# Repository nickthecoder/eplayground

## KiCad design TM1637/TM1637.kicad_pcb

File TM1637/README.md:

TM1637
======

The TM1637 can drive six eight segment displays, or a 6x8 LED matrix, as well as upto 16 buttons.

The module only has 8 buttons, however, you can switch between the two banks of buttons using a switch.

The outputs for the leds are exposed as simple header pins.

## Version History

### Version 1.0

At the time of writing, I haven't tested this module.

The name of the module is missing. It reads "Module Name". Oops.

### Version 1.1

Not printed.

Renamed the directory.
Corrected the module name.

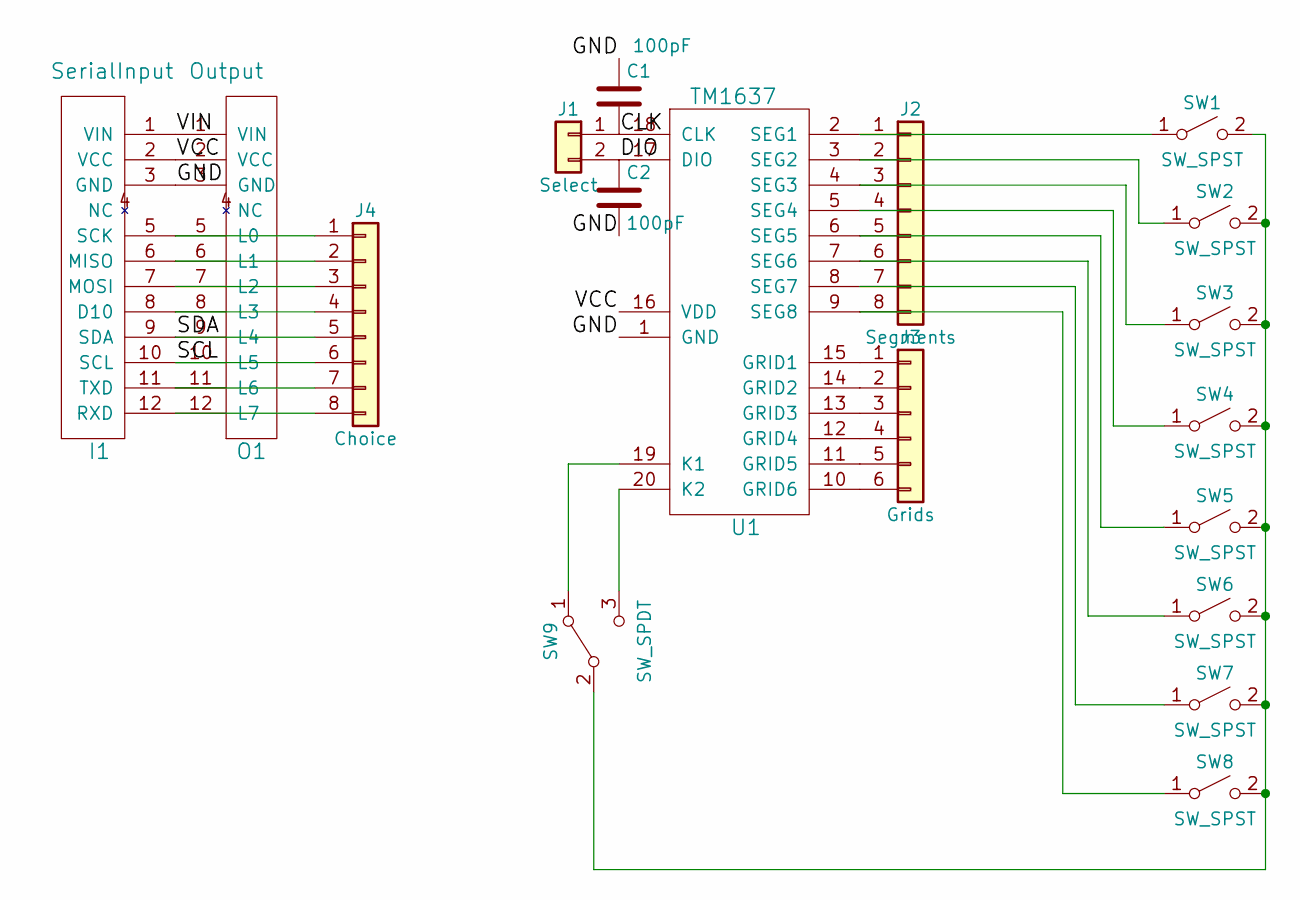
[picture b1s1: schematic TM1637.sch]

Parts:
C1, C2: 100pF; C_Disc_D3.0mm_W1.6mm_P2.50mm
I1: SerialInput; Pin_Header_Straight_1x12_Pitch2.54mm
J1: Select; Pin_Header_Straight_1x02_Pitch2.54mm
J2: Segments; Pin_Header_Straight_1x08_Pitch2.54mm
J3: Grids; Pin_Header_Straight_1x06_Pitch2.54mm
J4: Choice; Pin_Header_Straight_1x08_Pitch2.54mm
O1: Output; Socket_Strip_Straight_1x12_Pitch2.54mm
SW1, SW2, SW3, SW4, SW5, SW6, SW7, SW8: SW_SPST; SW_SPST_EVQP0
SW9: SW_SPDT; SW_CuK_JS202011CQN_DPDT_Straight
U1: TM1637; DIP-20_W7.62mm

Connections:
/CLK: C1.2, J1.1, U1.18 (CLK)
/DIO: C2.1, J1.2, U1.17 (DIO)
/GND: C1.1, C2.2, I1.3 (GND), O1.3 (GND), U1.1 (GND)
/SCL: I1.10 (SCL), J4.6, O1.10 (L5)
/SDA: I1.9 (SDA), J4.5, O1.9 (L4)
/VCC: I1.2 (VCC), O1.2 (VCC), U1.16 (VDD)
/VIN: I1.1 (VIN), O1.1 (VIN)
unnamed: I1.5 (SCK), J4.1, O1.5 (L0)
unnamed: I1.6 (MISO), J4.2, O1.6 (L1)
unnamed: I1.7 (MOSI), J4.3, O1.7 (L2)
unnamed: I1.8 (D10), J4.4, O1.8 (L3)
unnamed: I1.11 (TXD), J4.7, O1.11 (L6)
unnamed: I1.12 (RXD), J4.8, O1.12 (L7)
unnamed: J2.1, SW1.1 (A), U1.2 (SEG1)
unnamed: J2.2, SW2.1 (A), U1.3 (SEG2)
unnamed: J2.3, SW3.1 (A), U1.4 (SEG3)
unnamed: J2.4, SW4.1 (A), U1.5 (SEG4)
unnamed: J2.5, SW5.1 (A), U1.6 (SEG5)
unnamed: J2.6, SW6.1 (A), U1.7 (SEG6)
unnamed: J2.7, SW7.1 (A), U1.8 (SEG7)
unnamed: J2.8, SW8.1 (A), U1.9 (SEG8)
unnamed: J3.1, U1.15 (GRID1)
unnamed: J3.2, U1.14 (GRID2)
unnamed: J3.3, U1.13 (GRID3)
unnamed: J3.4, U1.12 (GRID4)
unnamed: J3.5, U1.11 (GRID5)
unnamed: J3.6, U1.10 (GRID6)
unnamed: SW1.2 (B), SW2.2 (B), SW3.2 (B), SW4.2 (B), SW5.2 (B), SW6.2 (B), SW7.2 (B), SW8.2 (B), SW9.2 (B)
unnamed: SW9.1 (A), U1.19 (K1)
unnamed: SW9.3 (C), U1.20 (K2)

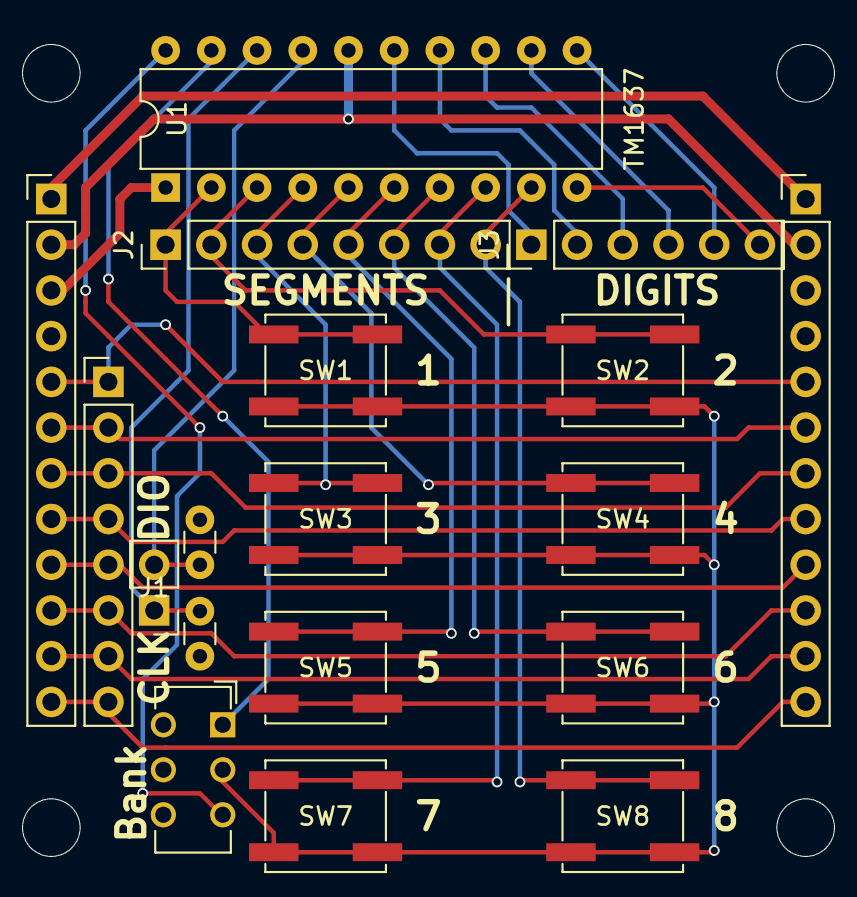
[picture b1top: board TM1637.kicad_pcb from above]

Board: 2 copper layers, 20 parts (0 on the bottom side), 30 nets.

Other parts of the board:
M3, M3#2: MountingHole_3.2mm_M3

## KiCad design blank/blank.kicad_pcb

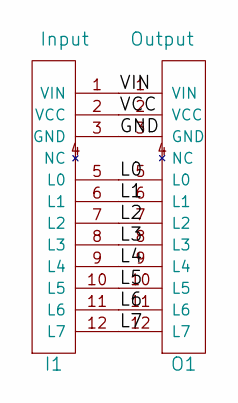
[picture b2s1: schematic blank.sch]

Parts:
I1: Input; Pin_Header_Straight_1x12_Pitch2.54mm
O1: Output; Socket_Strip_Straight_1x12_Pitch2.54mm

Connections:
/GND: I1.3 (GND), O1.3 (GND)
/L0: I1.5 (L0), O1.5 (L0)
/L1: I1.6 (L1), O1.6 (L1)
/L2: I1.7 (L2), O1.7 (L2)
/L3: I1.8 (L3), O1.8 (L3)
/L4: I1.9 (L4), O1.9 (L4)
/L5: I1.10 (L5), O1.10 (L5)
/L6: I1.11 (L6), O1.11 (L6)
/L7: I1.12 (L7), O1.12 (L7)
/VCC: I1.2 (VCC), O1.2 (VCC)
/VIN: I1.1 (VIN), O1.1 (VIN)

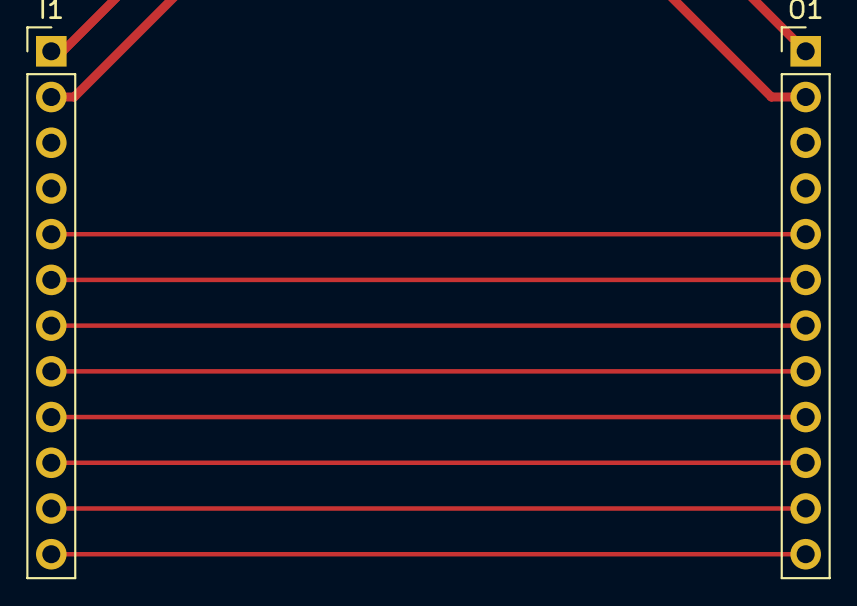
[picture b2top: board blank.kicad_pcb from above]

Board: 2 copper layers, 4 parts (0 on the bottom side), 11 nets.

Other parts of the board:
M3, M3#2: MountingHole_3.2mm_M3

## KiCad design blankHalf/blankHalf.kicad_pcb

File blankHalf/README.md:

I used this as a template for half-sized boards.
To keep costs low, I combine two half sized boards into one design, and have both printed
as if it were one board.

I have a router, which I can do my own V cuts, but its also easy to cut the boards using a sharp knife,
a little patience and brute force to snap them in two.

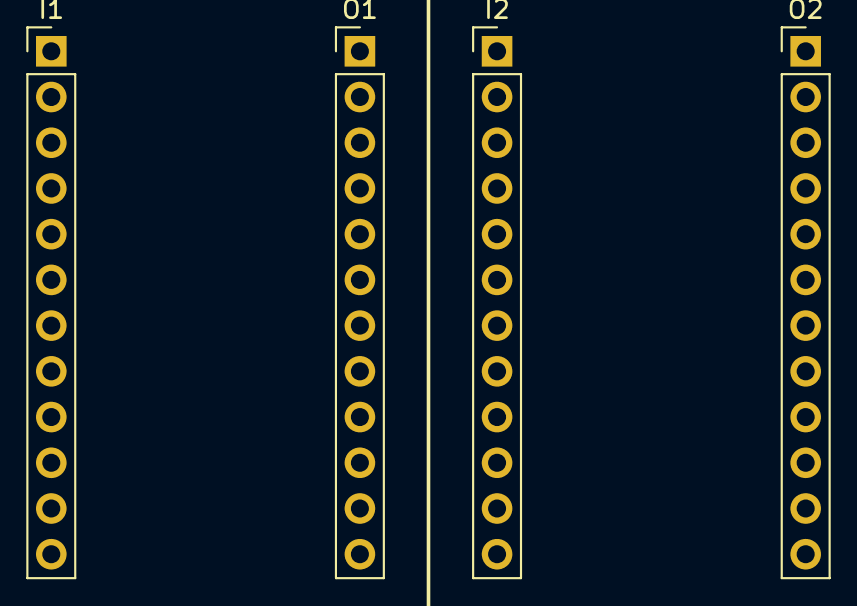
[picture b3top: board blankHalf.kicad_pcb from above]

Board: 2 copper layers, 6 parts (0 on the bottom side), 22 nets, no tracks yet.

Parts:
I1, I2: Input; Pin_Header_Straight_1x12_Pitch2.54mm
M3, M3#2: MountingHole_3.2mm_M3
O1, O2: Output; Socket_Strip_Straight_1x12_Pitch2.54mm

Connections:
/D0: I2.5, O2.5
/D1: I2.6, O2.6
/D2: I2.7, O2.7
/D3: I2.8, O2.8
/D4: I2.9, O2.9
/D5: I2.10, O2.10
/D6: I2.11, O2.11
/D7: I2.12, O2.12
/GND: I1.3, O1.3
/GND2: I2.3, O2.3
/L0: I1.5, O1.5
/L1: I1.6, O1.6
/L2: I1.7, O1.7
/L3: I1.8, O1.8
/L4: I1.9, O1.9
/L5: I1.10, O1.10
/L6: I1.11, O1.11
/L7: I1.12, O1.12
/VCC: I1.2, O1.2
/VCC2: I2.2, O2.2
/VIN: I1.1, O1.1
/VIN2: I2.1, O2.1

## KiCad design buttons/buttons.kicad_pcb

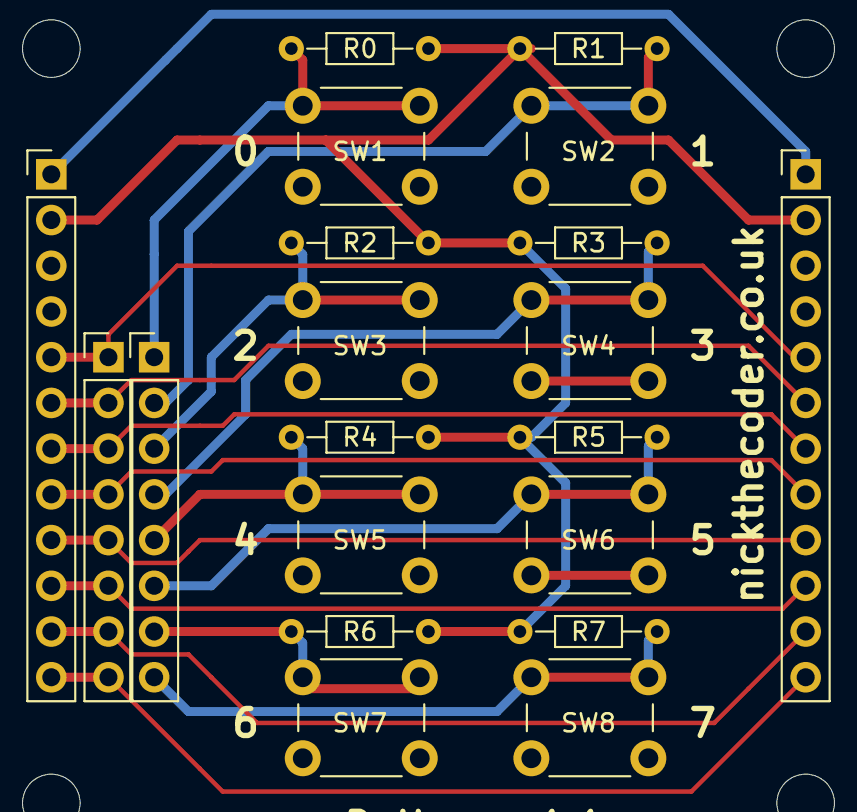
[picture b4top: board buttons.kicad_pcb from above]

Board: 2 copper layers, 22 parts (0 on the bottom side), 19 nets.

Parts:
H1: Choice; Pin_Header_Straight_1x08_Pitch2.54mm
H2: Select; Pin_Header_Straight_1x08_Pitch2.54mm
I1: Input; Pin_Header_Straight_1x12_Pitch2.54mm
M3, M3#2: MountingHole_3.2mm_M3
O1: Output; Pin_Header_Straight_1x12_Pitch2.54mm
R0, R1, R2, R3, R4, R5, R6, R7: 1K; R_Axial_DIN0204_L3.6mm_D1.6mm_P7.62mm_Horizontal
SW1, SW2, SW3, SW4, SW5, SW6, SW7, SW8: SW_Push; SW_PUSH_6mm

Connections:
/L0: H1.1, I1.5, O1.5
/L1: H1.2, I1.6, O1.6
/L2: H1.3, I1.7, O1.7
/L3: H1.4, I1.8, O1.8
/L4: H1.5, I1.9, O1.9
/L5: H1.6, I1.10, O1.10
/L6: H1.7, I1.11, O1.11
/L7: H1.8, I1.12, O1.12
/VCC: I1.2, O1.2, R0.1, R1.1, R2.1, R3.1, R4.1, R5.1, R6.1, R7.1
/VIN: I1.1, O1.1
Earth: I1.3, O1.3, SW1.2, SW2.2, SW3.2, SW4.2, SW5.2, SW6.2, SW7.2, SW8.2
unnamed: H2.1, R0.2, SW1.1
unnamed: H2.2, R1.2, SW2.1
unnamed: H2.3, R2.2, SW3.1
unnamed: H2.4, R3.2, SW4.1
unnamed: H2.5, R4.2, SW5.1
unnamed: H2.6, R5.2, SW6.1
unnamed: H2.7, R6.2, SW7.1
unnamed: H2.8, R7.2, SW8.1

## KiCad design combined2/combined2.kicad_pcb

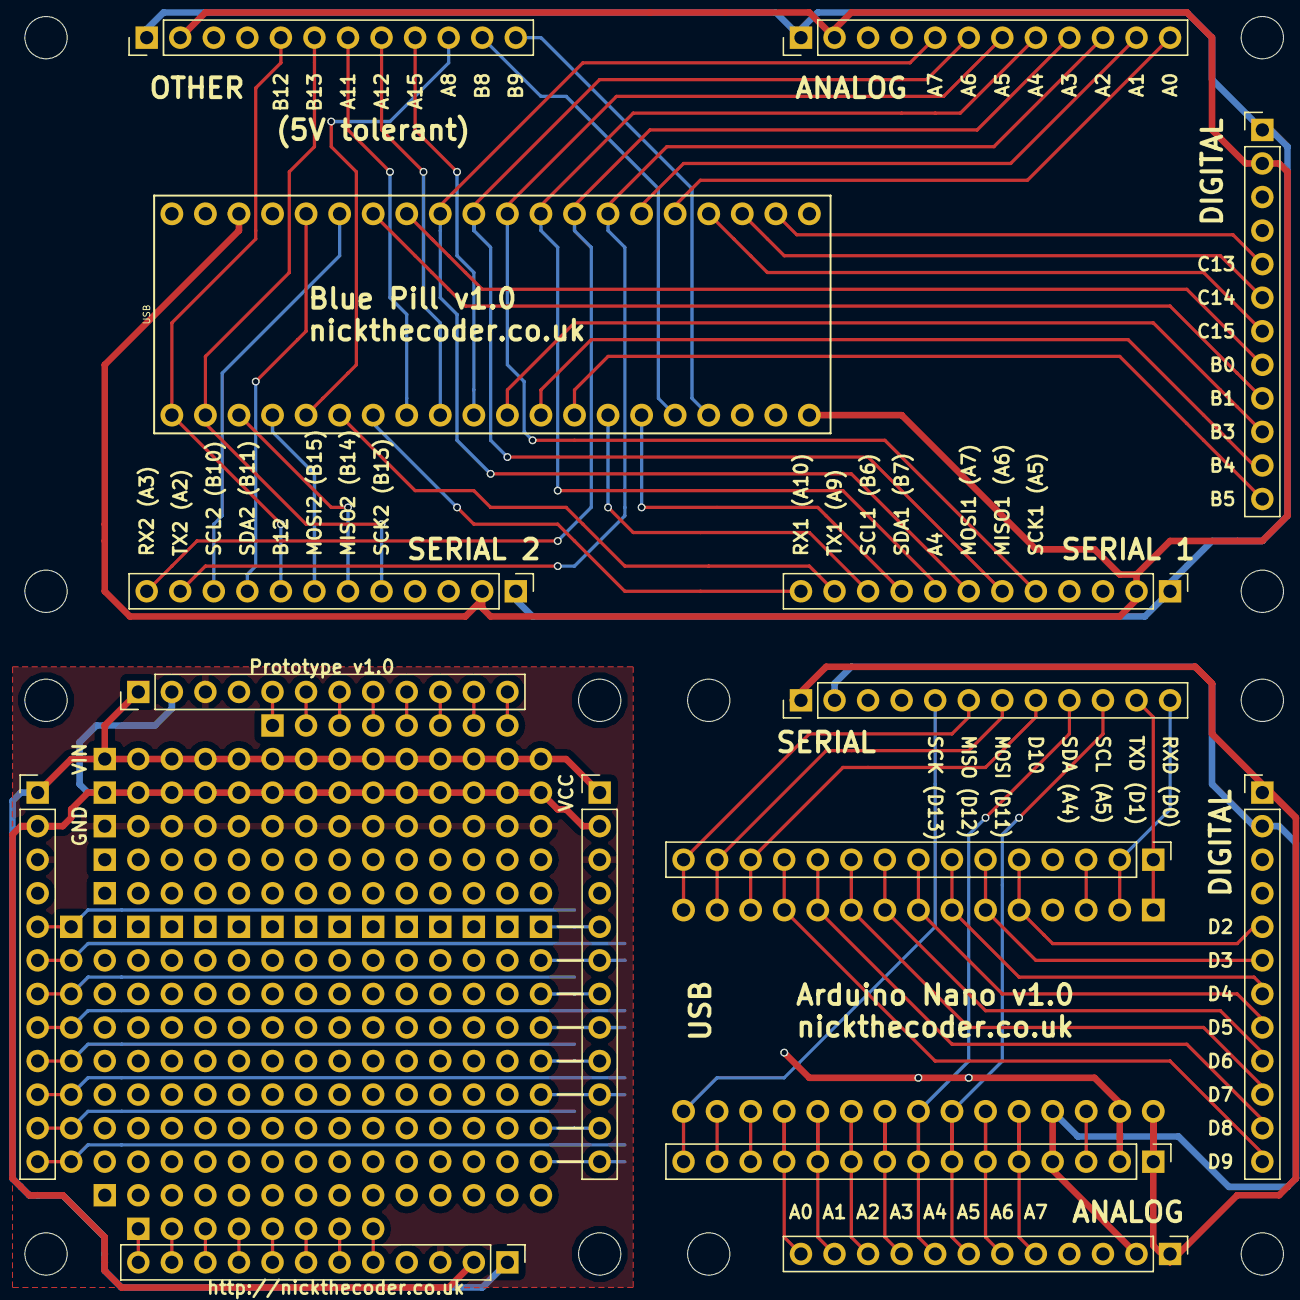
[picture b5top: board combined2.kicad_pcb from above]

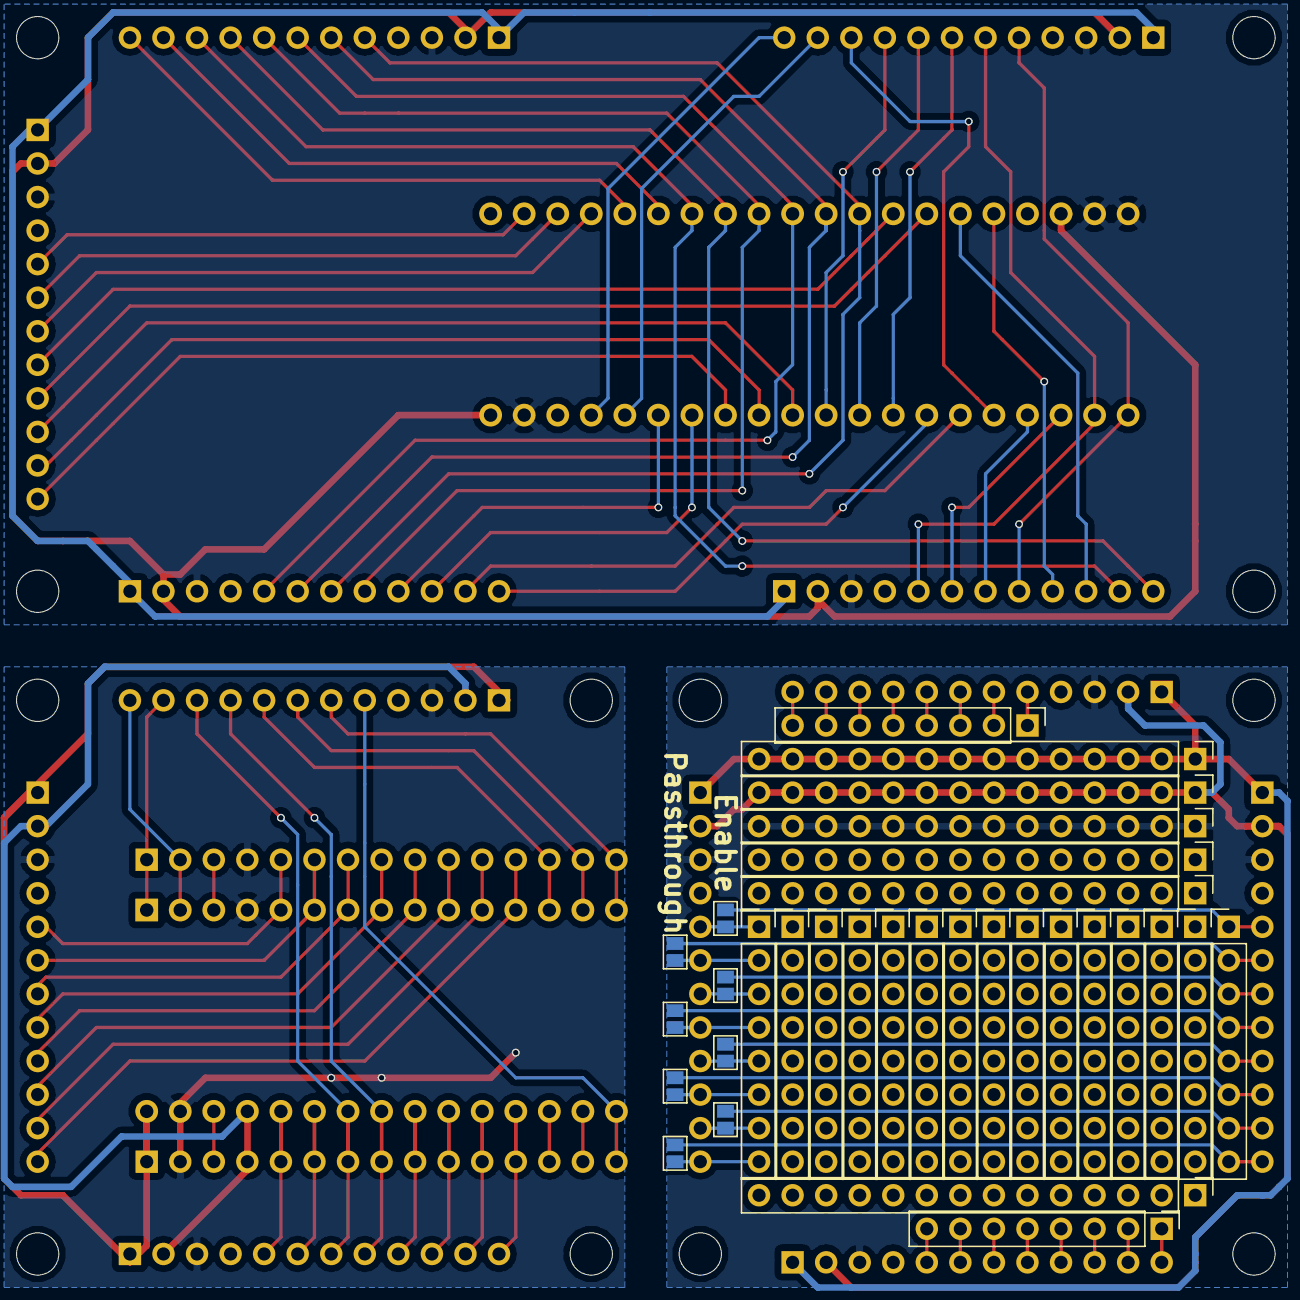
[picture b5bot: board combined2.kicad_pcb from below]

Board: 2 copper layers, 37 parts (15 on the bottom side), 86 nets.

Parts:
H1: Headers8L; Pin_Header_Straight_1x08_Pitch2.54mm
H4: Headers8; Pin_Header_Straight_1x08_Pitch2.54mm
I1, I2: Input; Pin_Header_Straight_1x12_Pitch2.54mm
J1, J2, J3, J4, J5, J6, J7, J8: GS2
J2#2: Header2; Pin_Header_Straight_1x15_Pitch2.54mm
J3#2: Header1; Pin_Header_Straight_1x15_Pitch2.54mm
J9, J10, J11: Conn_01x14; Pin_Header_Straight_1x14_Pitch2.54mm
J12, J13: Conn_01x08; Pin_Header_Straight_1x08_Pitch2.54mm
M3, M3#2: MountingHole_3.2mm_M3
O1, O1#3, O5: SerialOutput; Socket_Strip_Straight_1x12_Pitch2.54mm
O1#2, O2, O2#2, O2#3, O3, O3#2, O4: Output; Socket_Strip_Straight_1x12_Pitch2.54mm
U1: BluePill; bluePill
X: M3; MountingHole_3.2mm_M3
X#2, X#3, X#4: M3; MountingHole_3.2mm_M3
XA1: Arduino_Nano_Socket; Arduino_Nano

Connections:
/3V3: J2#2.14, XA1.3V3
/A0: J2#2.12, O3.12, O3#2.12, U1.5, XA1.A0
/A1: J2#2.11, O3.11, O3#2.11, U1.6, XA1.A1
/A2: J2#2.10, O3.10, O3#2.10, O5.11, U1.7, XA1.A2
/A3: J2#2.9, O3.9, O3#2.9, O5.12, U1.8, XA1.A3
/A4: J2#2.8, O1.8, O1#3.9, O3.8, O3#2.8, U1.9, XA1.A4
/A5: J2#2.7, O1.5, O1#3.10, O3.7, O3#2.7, U1.10, XA1.A5
/A6: J2#2.6, O1.6, O3.6, O3#2.6, U1.11, XA1.A6
/A7: J2#2.5, O1.7, O3.5, O3#2.5, U1.12, XA1.A7
/A8: O4.10, U1.25
/A9: O1.11, U1.26
/A10: O1.12, U1.27
/A11: O4.7, U1.28
/A12: O4.8, U1.29
/A15: O4.9, U1.30
/AREF: J2#2.13, XA1.AREF
/B0: O2.8, U1.13
/B1: O2.9, U1.14
/B3: O2.10, U1.31
/B4: O2.11, U1.32
/B5: O2.12, U1.33
/B6: O1.10, U1.34
/B7: O1.9, U1.35
/B8: O4.11, U1.36
/B9: O4.12, U1.37
/B10: O5.10, U1.15
/B11: O5.9, U1.16
/B12: O4.5, O5.8, U1.21
/B13: O4.6, O5.5, U1.22
/B14: O5.6, U1.23
/B15: O5.7, U1.24
/C13: O2.5, U1.2
/C14: O2.6, U1.3
/C15: O2.7, U1.4
/D0: J3#2.2, O1#3.12, XA1.D0
/D1: J3#2.1, O1#3.11, XA1.D1
/D2: J3#2.5, O2#3.5, XA1.D2
/D3: J3#2.6, O2#3.6, XA1.D3
/D4: J3#2.7, O2#3.7, XA1.D4
/D5: J3#2.8, O2#3.8, XA1.D5
/D6: J3#2.9, O2#3.9, XA1.D6
/D7: J3#2.10, O2#3.10, XA1.D7
/D8: J3#2.11, O2#3.11, XA1.D8
/D9: J3#2.12, O2#3.12, XA1.D9
/D10: J3#2.13, O1#3.8, XA1.D10
/D11: J3#2.14, O1#3.7, XA1.D11
/D12: J3#2.15, O1#3.6, XA1.D12
/D13: J2#2.15, O1#3.5, XA1.D13
/GND: J2#2.2, J3#2.4, O1.3, O1#3.3, O2.3, O2#3.3, O3.3, O3#2.3, O4.3, O5.3, U1.19, U1.20, U1.39, XA1.GND1, XA1.GND2
/L0: H1.1, I1.5, J1.2
/L1: H1.2, I1.6, J2.2
/L2: H1.3, I1.7, J3.2
/L3: H1.4, I1.8, J4.2
/L4: H1.5, I1.9, J5.2
/L5: H1.6, I1.10, J6.2
/L6: H1.7, I1.11, J7.2
/L7: H1.8, I1.12, J8.2
/Reset1: J3#2.3, XA1.RST1
/Reset2: J2#2.3, XA1.RST2
/VCC: I1.2, I2.2, J2#2.4, J10.1, J10.2, J10.3, J10.4, J10.5, J10.6, J10.7, J10.8, J10.9, J10.10, J10.11, J10.12, J10.13, J10.14, O1.2, O1#2.2, O1#3.2, O2.2, O2#2.2, O2#3.2, O3.2, O3#2.2, O4.2, O5.2, U1.18, U1.40, XA1.5V
/VIN: I1.1, I2.1, J2#2.1, J11.1, J11.2, J11.3, J11.4, J11.5, J11.6, J11.7, J11.8, J11.9, J11.10, J11.11, J11.12, J11.13, J11.14, O1.1, O1#2.1, O1#3.1, O2.1, O2#2.1, O2#3.1, O3.1, O3#2.1, O4.1, O5.1, XA1.VIN
Earth: I1.3, I2.3, J9.1, J9.2, J9.3, J9.4, J9.5, J9.6, J9.7, J9.8, J9.9, J9.10, J9.11, J9.12, J9.13, J9.14, O1#2.3, O2#2.3
unnamed: H4.1, J1.1, O2#2.5
unnamed: H4.2, J2.1, O2#2.6
unnamed: H4.3, J3.1, O2#2.7
unnamed: H4.4, J4.1, O2#2.8
unnamed: H4.5, J5.1, O2#2.9
unnamed: H4.6, J6.1, O2#2.10
unnamed: H4.7, J7.1, O2#2.11
unnamed: H4.8, J8.1, O2#2.12
unnamed: I2.5, J13.1
unnamed: I2.6, J13.2
unnamed: I2.7, J13.3
unnamed: I2.8, J13.4
unnamed: I2.9, J13.5
unnamed: I2.10, J13.6
unnamed: I2.11, J13.7
unnamed: I2.12, J13.8
unnamed: J12.1, O1#2.12
unnamed: J12.2, O1#2.11
unnamed: J12.3, O1#2.10
unnamed: J12.4, O1#2.9
unnamed: J12.5, O1#2.8
unnamed: J12.6, O1#2.7
unnamed: J12.7, O1#2.6
unnamed: J12.8, O1#2.5

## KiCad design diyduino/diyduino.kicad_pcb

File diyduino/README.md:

DIYDuino
========

An AT Mega 328 DIP chip, with a crystal and capacitor for the clock, plus a reset switch.

You can power the AT Mega via the ICSP header, or using the modules L7805 linear regulator, which takes power
from the VIN connection. (Power VIN, using a separate power module).

There are a pair of diodes, which allow both ICSP and a power module to be connected at the same time,
but this does mean that VCC will drop below 5V.

There are three standard connectors, in the same configuration as the Pro-Mini and Nano modules.

## Notes

I've incorrectly used "FTDI", on the scematic, when I should have used "ICSP".

The PWM capable pins are not indicated on the PCB. I suggest adding a dot of paint on the sockets.

The AT Mega 328 DIP chip does not have an A6 and A7, so the analog connector only has 6 inputs.

I've left enough space around the AT Mega, so that a narrow ZIF socket can be used.
This will obscure some fo the Serial connector's pin labels though.

## Soldering Notes

There are two sets of ICSP header, with TX and RX reversed. Only populate one, the choice is yours.
Note, I think right angled headers make more sense than straight.
The lables of TX and RX can be confusing, because they depend on your point of view.
(A receive is somebody else's transmit!). These are labelled from the AT Mega's point of view.

## Version History

### Version 1.0

Printed, but untested

### Version 1.1

Not printed

Moved the C3 capacitor, further away from the crystal (the footprint for my crystals is larger than the footprint in KICAD).

Change the position of the voltage regulator, so that it isn't pointing its heat directly at the electrolytic capacitors.

Added an "S" above A4 and A5 to hint that they are also used by the Serial connector.

Added a jumper for AREF and VCC, so that AREF can be set to VCC, or another value if needed.

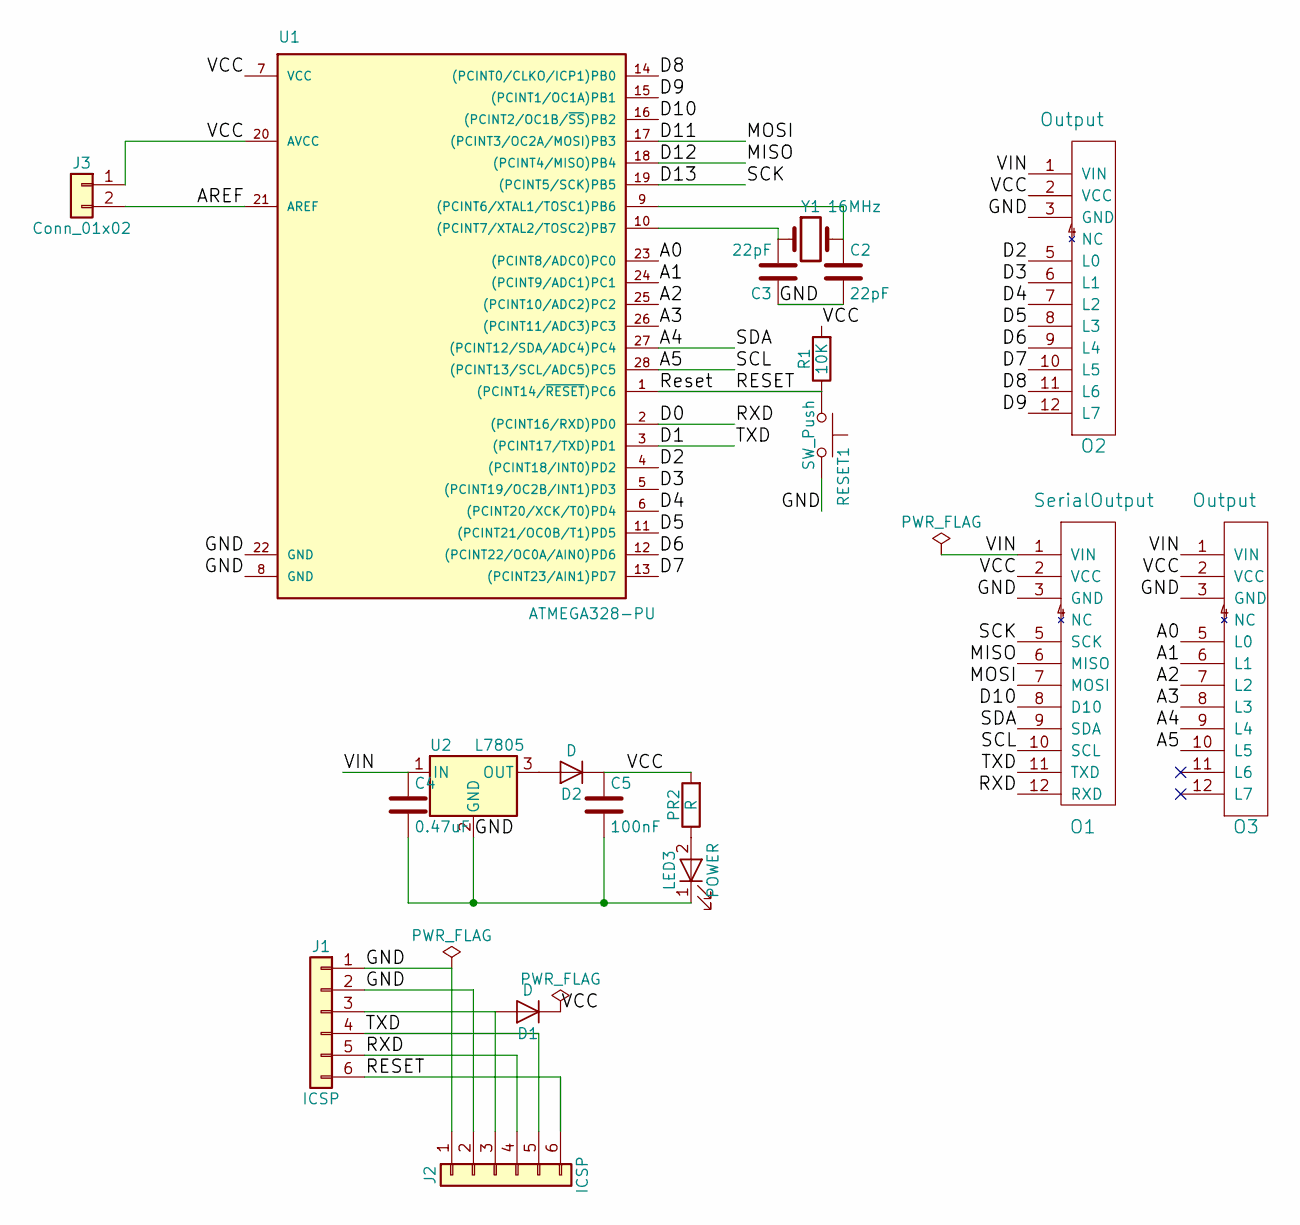
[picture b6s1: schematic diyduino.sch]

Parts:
C2, C3: 22pF; C_Disc_D3.0mm_W1.6mm_P2.50mm
C4: 0.47uF; CP_Radial_D6.3mm_P2.50mm
C5: 100nF; CP_Radial_D6.3mm_P2.50mm
D1, D2: D; D_T-1_P5.08mm_Horizontal
J1, J2: ICSP; Pin_Header_Straight_1x06_Pitch2.54mm
J3: Conn_01x02; Pin_Header_Straight_1x02_Pitch2.54mm
LED3: POWER; LED_Rectangular_W3.0mm_H2.0mm
O1: SerialOutput; Socket_Strip_Straight_1x12_Pitch2.54mm
O2, O3: Output; Socket_Strip_Straight_1x12_Pitch2.54mm
PR2: R; R_Axial_DIN0204_L3.6mm_D1.6mm_P7.62mm_Horizontal
R1: 10K; R_Axial_DIN0204_L3.6mm_D1.6mm_P7.62mm_Horizontal
RESET1: SW_Push; SW_PUSH_6mm
U1: ATMEGA328-PU; DIP-28_W7.62mm
U2: L7805; TO-220
Y1: 16MHz; Resonator-2pin_w6.0mm_h3.0mm

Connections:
/A0: O3.5 (L0), U1.23 ((PCINT8/ADC0)PC0)
/A1: O3.6 (L1), U1.24 ((PCINT9/ADC1)PC1)
/A2: O3.7 (L2), U1.25 ((PCINT10/ADC2)PC2)
/A3: O3.8 (L3), U1.26 ((PCINT11/ADC3)PC3)
/A4: O1.9 (SDA), O3.9 (L4), U1.27 ((PCINT12/SDA/ADC4)PC4)
/A5: O1.10 (SCL), O3.10 (L5), U1.28 ((PCINT13/SCL/ADC5)PC5)
/AREF: J3.2, U1.21 (AREF)
/D0: J1.5, J2.4, O1.12 (RXD), U1.2 ((PCINT16/RXD)PD0)
/D1: J1.4, J2.5, O1.11 (TXD), U1.3 ((PCINT17/TXD)PD1)
/D2: O2.5 (L0), U1.4 ((PCINT18/INT0)PD2)
/D3: O2.6 (L1), U1.5 ((PCINT19/OC2B/INT1)PD3)
/D4: O2.7 (L2), U1.6 ((PCINT20/XCK/T0)PD4)
/D5: O2.8 (L3), U1.11 ((PCINT21/OC0B/T1)PD5)
/D6: O2.9 (L4), U1.12 ((PCINT22/OC0A/AIN0)PD6)
/D7: O2.10 (L5), U1.13 ((PCINT23/AIN1)PD7)
/D8: O2.11 (L6), U1.14 ((PCINT0/CLKO/ICP1)PB0)
/D9: O2.12 (L7), U1.15 ((PCINT1/OC1A)PB1)
/D10: O1.8 (D10), U1.16 ((PCINT2/OC1B/~SS~)PB2)
/D11: O1.7 (MOSI), U1.17 ((PCINT3/OC2A/MOSI)PB3)
/D12: O1.6 (MISO), U1.18 ((PCINT4/MISO)PB4)
/D13: O1.5 (SCK), U1.19 ((PCINT5/SCK)PB5)
/GND: C2.2, C3.1, C4.2, C5.2, J1.1, J1.2, J2.1, J2.2, LED3.1 (K), O1.3 (GND), O2.3 (GND), O3.3 (GND), RESET1.2, U1.8 (GND), U1.22 (GND), U2.2 (GND)
/RESET: J1.6, J2.6, R1.1, RESET1.1, U1.1 ((PCINT14/~RESET~)PC6)
/VCC: C5.1, D1.1 (K), D2.1 (K), J3.1, O1.2 (VCC), O2.2 (VCC), O3.2 (VCC), PR2.2, R1.2, U1.7 (VCC), U1.20 (AVCC)
/VIN: C4.1, O1.1 (VIN), O2.1 (VIN), O3.1 (VIN), U2.1 (IN)
unnamed: C2.1, U1.9 ((PCINT6/XTAL1/TOSC1)PB6), Y1.2
unnamed: C3.2, U1.10 ((PCINT7/XTAL2/TOSC2)PB7), Y1.1
unnamed: D1.2 (A), J1.3, J2.3
unnamed: D2.2 (A), U2.3 (OUT)
unnamed: LED3.2 (A), PR2.1

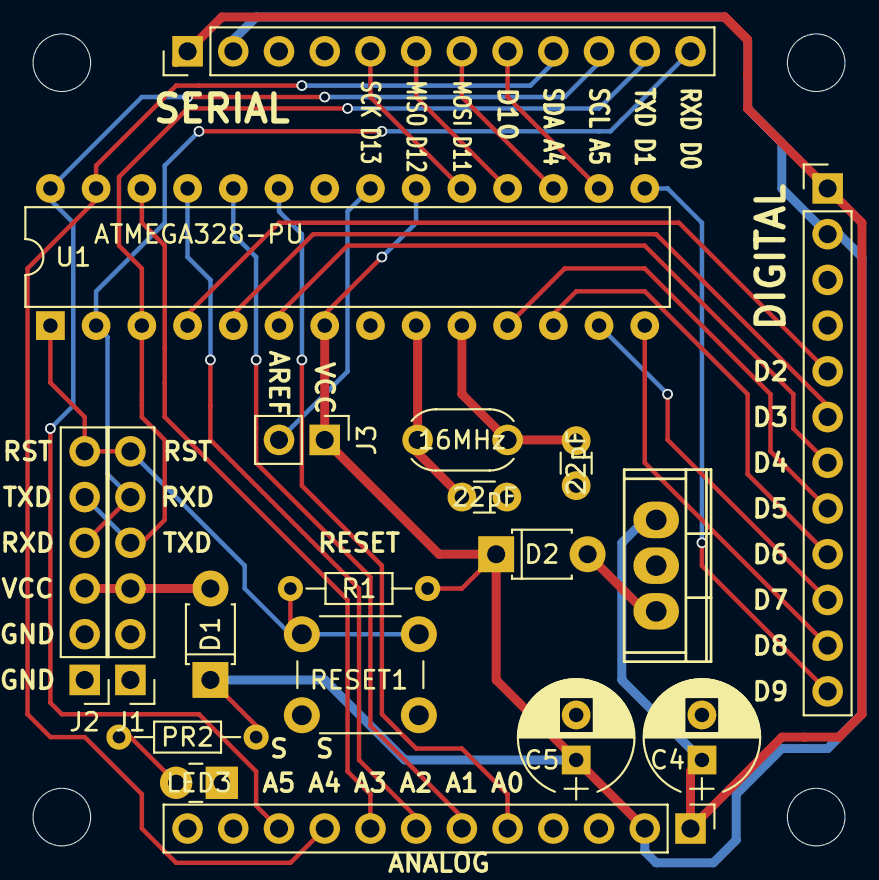
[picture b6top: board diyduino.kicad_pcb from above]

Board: 2 copper layers, 21 parts (0 on the bottom side), 30 nets.

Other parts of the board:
X: M3; MountingHole_3.2mm_M3
X#2: M3; MountingHole_3.2mm_M3

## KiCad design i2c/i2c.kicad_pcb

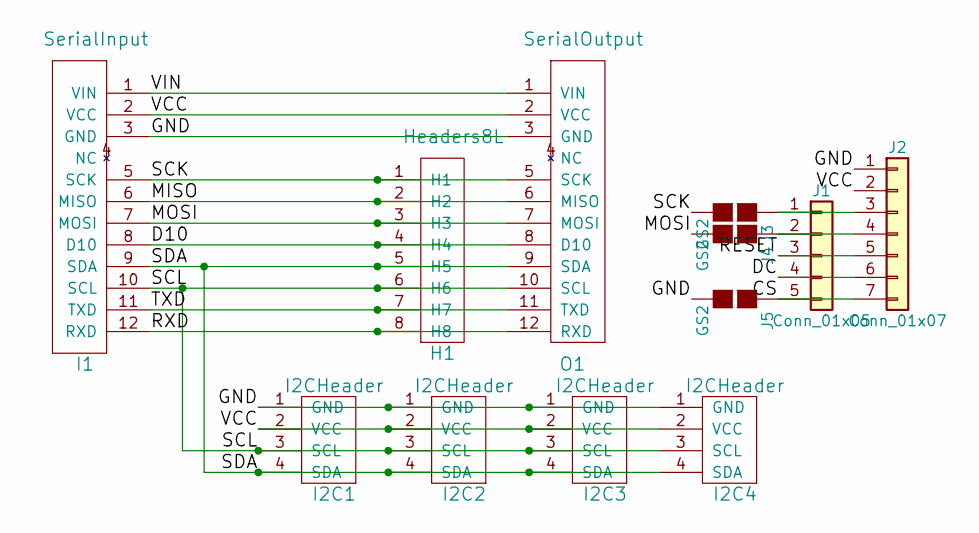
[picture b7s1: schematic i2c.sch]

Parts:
H1: Headers8L; Pin_Header_Straight_1x08_Pitch2.54mm
I1: SerialInput; Socket_Strip_Straight_1x12_Pitch2.54mm
I2C1, I2C2, I2C3, I2C4: I2CHeader; Socket_Strip_Straight_1x04_Pitch2.54mm
J1: Conn_01x05; Pin_Header_Straight_1x05_Pitch2.54mm
J2: Conn_01x07; Pin_Header_Straight_1x07_Pitch2.54mm
J3, J4, J5: GS2
O1: SerialOutput; Socket_Strip_Straight_1x12_Pitch2.54mm

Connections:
/CS: J1.5, J2.7, J5.1 (G1)
/D10: H1.4 (H4), I1.8 (D10), O1.8 (D10)
/DC: J1.4, J2.6
/GND: I1.3 (GND), I2C1.1 (GND), I2C2.1 (GND), I2C3.1 (GND), I2C4.1 (GND), J2.1, J5.2 (G2), O1.3 (GND)
/MISO: H1.2 (H2), I1.6 (MISO), O1.6 (MISO)
/MOSI: H1.3 (H3), I1.7 (MOSI), J4.2 (G2), O1.7 (MOSI)
/RESET: J1.3, J2.5
/RXD: H1.8 (H8), I1.12 (RXD), O1.12 (RXD)
/SCK: H1.1 (H1), I1.5 (SCK), J3.2 (G2), O1.5 (SCK)
/SCL: H1.6 (H6), I1.10 (SCL), I2C1.3 (SCL), I2C2.3 (SCL), I2C3.3 (SCL), I2C4.3 (SCL), O1.10 (SCL)
/SDA: H1.5 (H5), I1.9 (SDA), I2C1.4 (SDA), I2C2.4 (SDA), I2C3.4 (SDA), I2C4.4 (SDA), O1.9 (SDA)
/TXD: H1.7 (H7), I1.11 (TXD), O1.11 (TXD)
/VCC: I1.2 (VCC), I2C1.2 (VCC), I2C2.2 (VCC), I2C3.2 (VCC), I2C4.2 (VCC), J2.2, O1.2 (VCC)
/VIN: I1.1 (VIN), O1.1 (VIN)
unnamed: J1.1, J2.3, J3.1 (G1)
unnamed: J1.2, J2.4, J4.1 (G1)

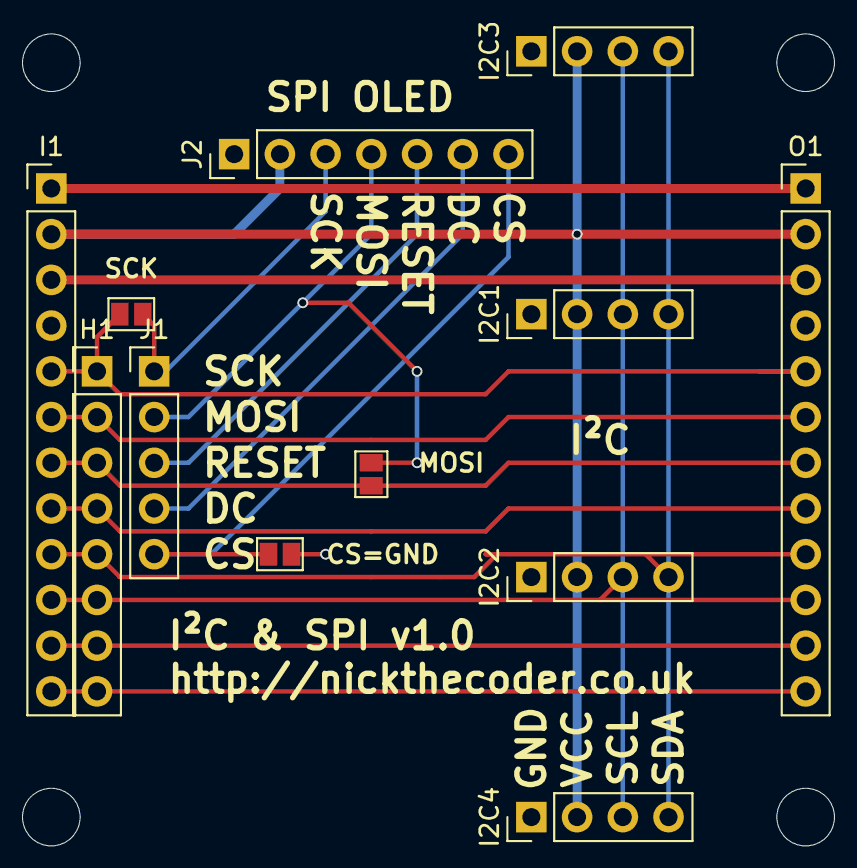
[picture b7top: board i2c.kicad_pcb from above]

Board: 2 copper layers, 14 parts (0 on the bottom side), 16 nets.

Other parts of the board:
M3, M3#2: MountingHole_3.2mm_M3
